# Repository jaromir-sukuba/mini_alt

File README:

Those are design files for mini altimeter. More at my hackaday project page

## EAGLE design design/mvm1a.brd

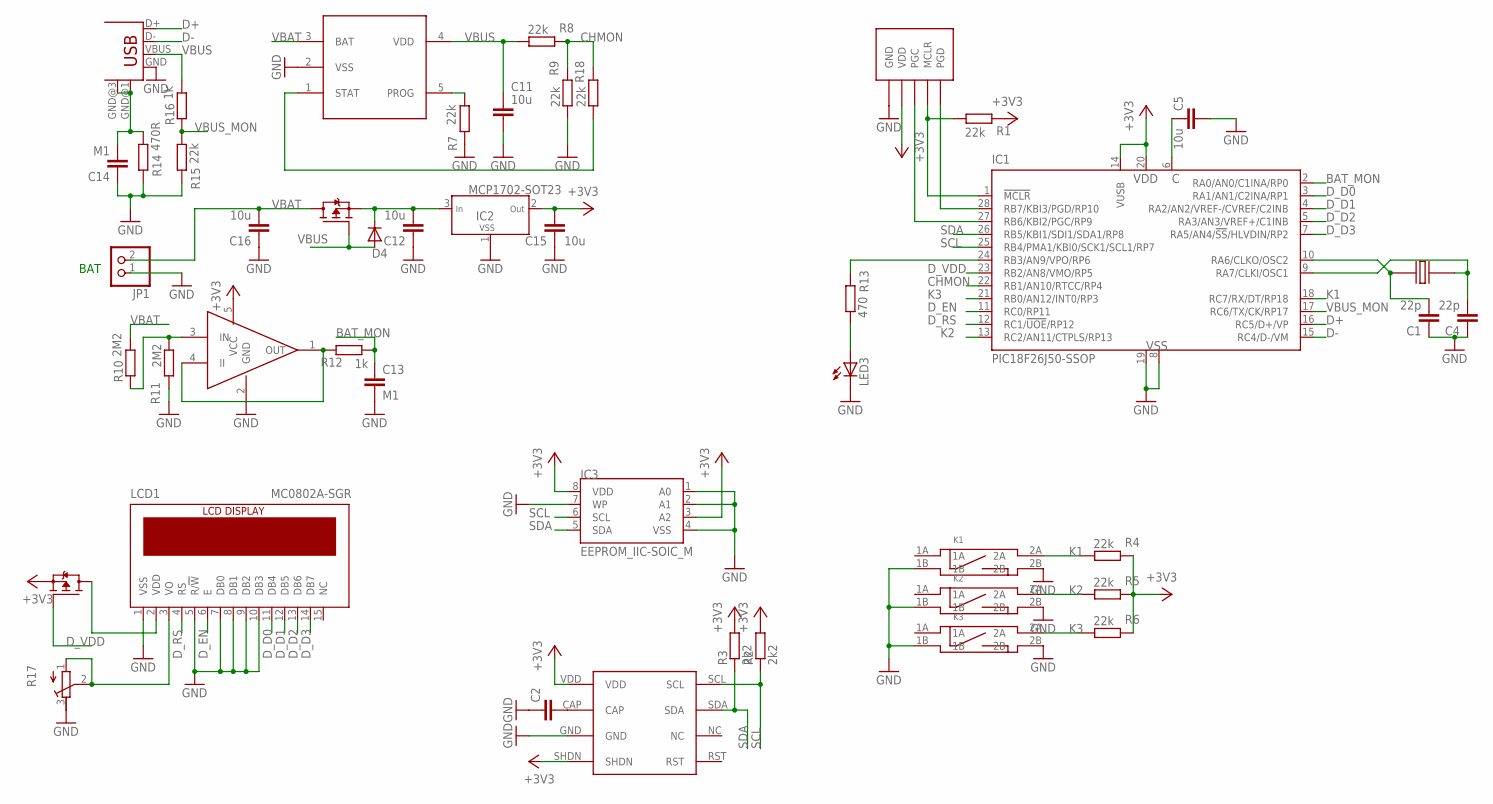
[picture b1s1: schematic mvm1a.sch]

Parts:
C1, C4: 22p; 0603
C2: C_0603; 0603
C5, C11, C12, C16: 10u; R0805
C13, C14: M1; 0603
C15: 10u; 0603
D4: DIODE-SOD123; SOD123
IC1: PIC18F26J50-SSOP; SSOP28
IC2: MCP1702-SOT23; SOT23
IC3: EEPROM_IIC-SOIC_M; SO-08_208
JP1: PINHD-1X02_2.54-90°; 1X02/90
K1, K2, K3: SWITCH_BD_B; SW_SMD2
LCD1: MC0802A-SGR; MC0802
LED3: LEDCHIPLED_0805; CHIPLED_0805
R1, R4, R5, R6, R7, R8, R9, R15, R18: 22k; 0603
R2, R3: 2k2; 0603
R10, R11: 2M2; 0603
R12, R16: 1k; 0603
R13: 470; 0603
R14: 470R; 0603
R17: R-TRIMM4G/J; RTRIM4G/J
U$1: PROGHEAD; PROGHEAD_2
U$2, U$4: BSS84; SOT23-3
U$3: MCP73831; SOT23-5
U$5: MCP6001; SOT23-5
U$6: MPL115A
USB2: USB-MB-S
X3: CRYST_TC26TC38; TC38

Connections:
+3V3: C15.2, IC1.14 (VUSB), IC1.20 (VDD), IC2.2 (OUT), IC3.3 (A2), IC3.8 (VDD), R1.1, R2.2, R3.2, R4.1, R5.1, R6.1, U$1.VDD, U$2.2 (S), U$5.5 (VCC), U$6.SHDN, U$6.VDD
BAT_MON: C13.1, IC1.2 (RA0/AN0/C1INA/RP0), R12.1
CHMON: IC1.22 (RB1/AN10/RTCC/RP4), R8.1, R9.1, R18.1
D+: IC1.16 (RC5/D+/VP), USB2.D+
D-: IC1.15 (RC4/D-/VM), USB2.D-
D_D0: IC1.3 (RA1/AN1/C2INA/RP1), LCD1.11 (DB4)
D_D1: IC1.4 (RA2/AN2/VREF-/CVREF/C2INB), LCD1.12 (DB5)
D_D2: IC1.5 (RA3/AN3/VREF+/C1INB), LCD1.13 (DB6)
D_D3: IC1.7 (RA5/AN4/!SS!/HLVDIN/RP2), LCD1.14 (DB7)
D_EN: IC1.11 (RC0/RP11), LCD1.6 (E)
D_RS: IC1.12 (RC1/!UOE!/RP12), LCD1.4 (RS)
D_VDD: IC1.23 (RB2/AN8/VMO/RP5), U$2.1 (G)
GND: C1.1, C2.1, C4.1, C5.2, C11.2, C12.1, C13.2, C14.1, C15.1, C16.1, IC1.8 (VSS), IC1.19 (VSS), IC2.1 (VSS), IC3.1 (A0), IC3.2 (A1), IC3.4 (VSS), IC3.7 (WP), JP1.1, K1.1B, K1.2B, K2.1B, K2.2B, K3.1B, K3.2B, LCD1.1 (VSS), LCD1.5 (R/!W), LCD1.7 (DB0), LCD1.8 (DB1), LCD1.9 (DB2), LCD1.10 (DB3), LED3.C, R7.1, R9.2, R11.2, R14.1, R15.1, R17.3 (A), U$1.GND, U$3.2 (VSS), U$5.2 (GND), U$6.GND, USB2.GND
K1: IC1.18 (RC7/RX/DT/RP18), K1.2A, R4.2
K2: IC1.13 (RC2/AN11/CTPLS/RP13), K2.2A, R5.2
K3: IC1.21 (RB0/AN12/INT0/RP3), K3.2A, R6.2
unnamed: IC1.24 (RB3/AN9/VPO/RP6), R13.2
unnamed: IC1.28 (RB7/KBI3/PGD/RP10), U$1.PGD
unnamed: IC1.27 (RB6/KBI2/PGC/RP9), U$1.PGC
unnamed: IC1.1 (!MCLR), R1.2, U$1.MCLR
unnamed: LCD1.2 (VDD), U$2.3 (D)
unnamed: C1.2, IC1.10 (RA6/CLKO/OSC2), X3.P$1
unnamed: C14.2, R14.2, USB2.GND@1 (GND), USB2.GND@3 (GND)
unnamed: C12.2, D4.C, IC2.3 (IN), U$4.2 (S)
unnamed: R12.2, U$5.1 (OUT), U$5.4 (II)
unnamed: R10.1, R11.1, U$5.3 (IN)
unnamed: C2.2, U$6.CAP
unnamed: C4.2, IC1.9 (RA7/CLKI/OSC1), X3.P$2
unnamed: C5.1, IC1.6 (VDDCORE/VCAP)
unnamed: LED3.A, R13.1
unnamed: LCD1.3 (VO), R17.1 (E), R17.2 (S)
unnamed: R7.2, U$3.5 (PROG)
unnamed: R18.2, U$3.1 (STAT)
SCL: IC1.25 (RB4/PMA1/KBI0/SCK1/SCL1/RP7), IC3.6 (SCL), R2.1, U$6.SCL
SDA: IC1.26 (RB5/KBI1/SDI1/SDA1/RP8), IC3.5 (SDA), R3.1, U$6.SDA
VBAT: C16.2, JP1.2, R10.2, U$3.3 (BAT), U$4.3 (D)
VBUS: C11.1, D4.A, R8.2, R16.2, U$3.4 (VDD), U$4.1 (G), USB2.VBUS
VBUS_MON: IC1.17 (RC6/TX/CK/RP17), R15.2, R16.1

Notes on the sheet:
BAT

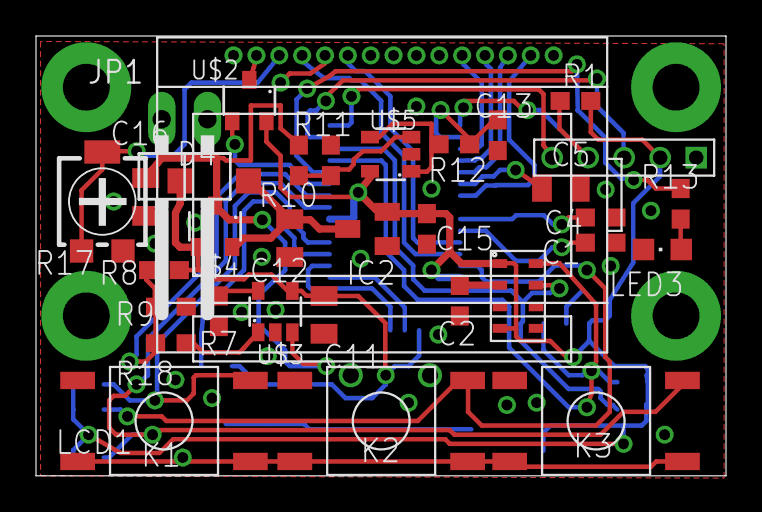
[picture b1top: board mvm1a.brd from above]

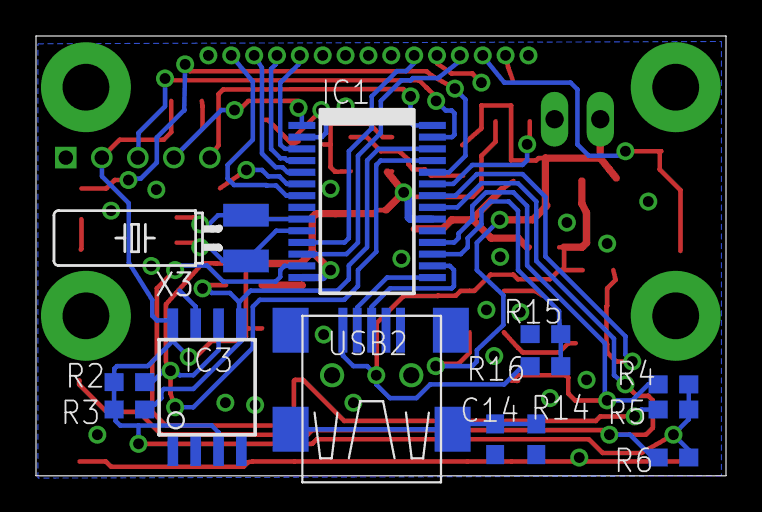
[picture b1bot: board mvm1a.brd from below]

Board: 2 copper layers, 38.3 x 24.4 mm, 46 parts (13 on the bottom side), 38 nets.

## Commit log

2014-03-31 ver 1
    first release
2014-03-31 ver 1
    first revision
2014-05-19 ver 2
    added logging function
